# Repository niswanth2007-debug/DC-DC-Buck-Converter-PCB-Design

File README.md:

# LM2596T-5 DC to DC Buck Converter

A fixed 5V output buck converter PCB designed using KiCad as a first PCB design project.
This board steps down a higher DC voltage (7V–40V) to a stable 5V output using the
LM2596T-5 switching regulator IC.

---

## Overview

Buck converters are switching regulators that efficiently step down voltage with
minimal heat compared to linear regulators like the 7805. This design uses the
LM2596T-5, a fixed 5V variant that requires minimal external components while
delivering up to 3A of output current.

The board includes:
- An ON/OFF push button switch for manual control
- An LED power indicator with current limiting resistor
- Input and output screw terminals for easy wiring
- Flyback diode (1N5822) for protection
- Input and output filter capacitors for stable operation

---

## PCB Images

### Schematic

### 3D Tilted View

### 3D Top View

### Footprint Assignments

### PCB Editor View

---

## Schematic Overview

The circuit follows the standard LM2596 application circuit:
- **VIN** receives input from J2 screw terminal through C1 (680µF filter cap)
- **SW1** (push button) controls the ON/OFF pin of the LM2596
- **OUT** drives current through L1 (33µH inductor) to the output
- **D1** (1N5822 Schottky diode) acts as a freewheeling diode
- **C2** (220µF) filters the output voltage
- **FB** pin is tied to fixed 5V reference internally
- Output feeds J1 screw terminal with R1+D2 as a power indicator LED

---

## Components / Bill of Materials

| Ref  | Value      | Description                        | Footprint                        |
|------|------------|------------------------------------|----------------------------------|
| U1   | LM2596T-5  | Fixed 5V Buck Regulator IC         | TO-220-5, P3.4x3.7mm            |
| L1   | 33µH       | Inductor                           | Axial, L5.3mm D2.2mm P7.62mm   |
| C1   | 680µF      | Input Filter Capacitor             | Axial, L5.1mm D3.1mm P10.00mm  |
| C2   | 220µF      | Output Filter Capacitor            | Axial, L5.1mm D3.1mm P10.00mm  |
| D1   | 1N5822     | Schottky Freewheeling Diode        | DO-41, SOD81 P7.62mm            |
| D2   | LED        | Power Indicator LED                | LED_D3.0mm                      |
| R1   | 15Ω        | LED Current Limiting Resistor      | Axial, DIN0204 L3.6mm P5.08mm  |
| SW1  | SW_Push    | ON/OFF Push Button Switch          | SW_PUSH_6mm                     |
| J1   | Screw Term | Output Terminal (2-pin)            | Phoenix MKDS-1,5 2-pin          |
| J2   | Screw Term | Input Terminal (2-pin)             | Phoenix MKDS-1,5 2-pin          |

---

## Specifications

| Parameter           | Value          |
|--------------------|----------------|
| Input Voltage      | 7V – 40V DC    |
| Output Voltage     | 5V DC (Fixed)  |
| Max Output Current | Up to 3A       |
| Switching Frequency| 150kHz         |
| Efficiency         | Up to ~85%     |
| Inductor           | 33µH           |

---

## How to Use

### Input
Connect a DC power source (7V–40V) to the **J2** screw terminal:
- J2 Pin 1 → Positive (+)
- J2 Pin 2 → Negative (GND)

### Output
Connect your load to the **J1** screw terminal:
- J1 Pin 1 → 5V Output (+)
- J1 Pin 2 → Negative (GND)

### Power Switch
Press **SW1** to toggle the converter ON or OFF.
The **D2 LED** will light up when the output is active.

---

## How to Open in KiCad

1. Install [KiCad](https://www.kicad.org/) (version 9 or later recommended)
2. Clone or download this repository
3. Open `project 3.kicad_pro` in KiCad
4. Schematic is in `project 3.kicad_sch`
5. PCB layout is in `project 3.kicad_pcb`

---

## Generating Gerber Files

Gerber files are not included but can be easily generated:

1. Open `project 3.kicad_pcb` in KiCad PCB Editor
2. Go to **File → Plot**
3. Select layers: F.Cu, B.Cu, F.Silkscreen, B.Silkscreen,
   F.Mask, B.Mask, Edge.Cuts
4. Click **Plot**
5. Click **Generate Drill Files**
6. Submit output folder to your PCB manufacturer (JLCPCB, PCBWay, etc.)

---

## What I Learned

- KiCad schematic capture and PCB layout workflow
- Footprint assignment and 3D visualization
- Buck converter operating principles
- Through-hole component placement and routing
- Design rule checks (DRC) in KiCad

---

## Author

**Niswanth B**
Student ID: 128004168

*First KiCad PCB Design Project*

---

## License

This project is open source under the [MIT License](LICENSE).
Feel free to use, modify, and learn from it.

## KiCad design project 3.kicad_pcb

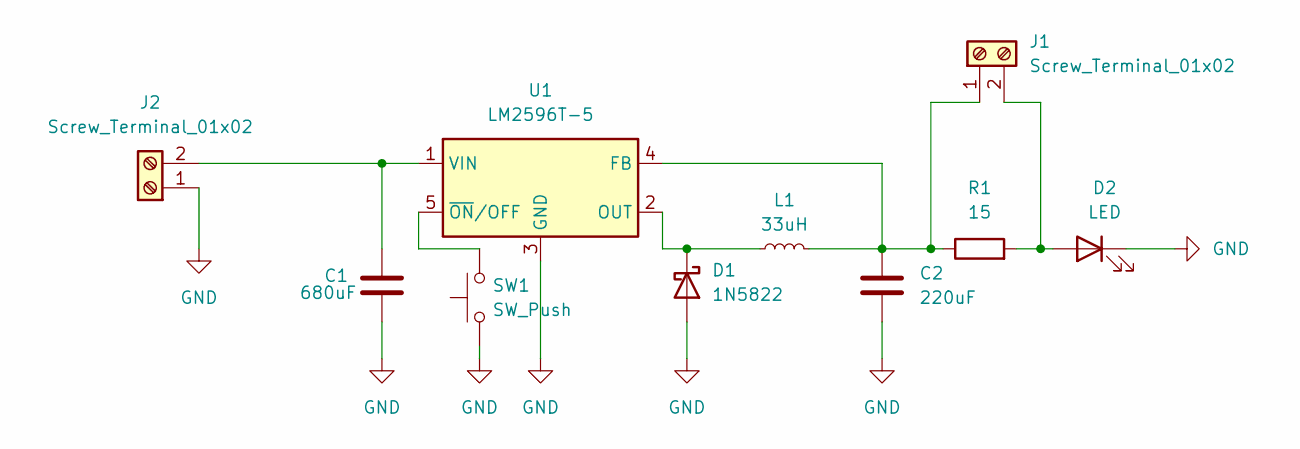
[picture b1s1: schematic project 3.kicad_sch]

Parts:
C1: 680uF; C_Axial_L5.1mm_D3.1mm_P10.00mm_Horizontal
C2: 220uF; C_Axial_L5.1mm_D3.1mm_P10.00mm_Horizontal
D1: 1N5822; D_DO-41_SOD81_P7.62mm_Horizontal
D2: LED; LED_D3.0mm
J1, J2: Screw_Terminal_01x02; TerminalBlock_Phoenix_MKDS-1,5-2_1x02_P5.00mm_Horizontal
L1: 33uH; L_Axial_L5.3mm_D2.2mm_P7.62mm_Horizontal_Vishay_IM-1
R1: 15; R_Axial_DIN0204_L3.6mm_D1.6mm_P5.08mm_Horizontal
SW1: SW_Push; SW_PUSH_6mm
U1: LM2596T-5; TO-220-5_P3.4x3.7mm_StaggerOdd_Lead3.8mm_Vertical

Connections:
GND: C1.2, C2.2, D1.2 (A), D2.1 (K), J2.1, SW1.1, U1.3 (GND)
unnamed: D1.1 (K), L1.1, U1.2 (OUT)
unnamed: D2.2 (A), J1.2, R1.2
unnamed: C2.1, J1.1, L1.2, R1.1, U1.4 (FB)
unnamed: C1.1, J2.2, U1.1 (VIN)
unnamed: SW1.2, U1.5 (~ON/OFF)

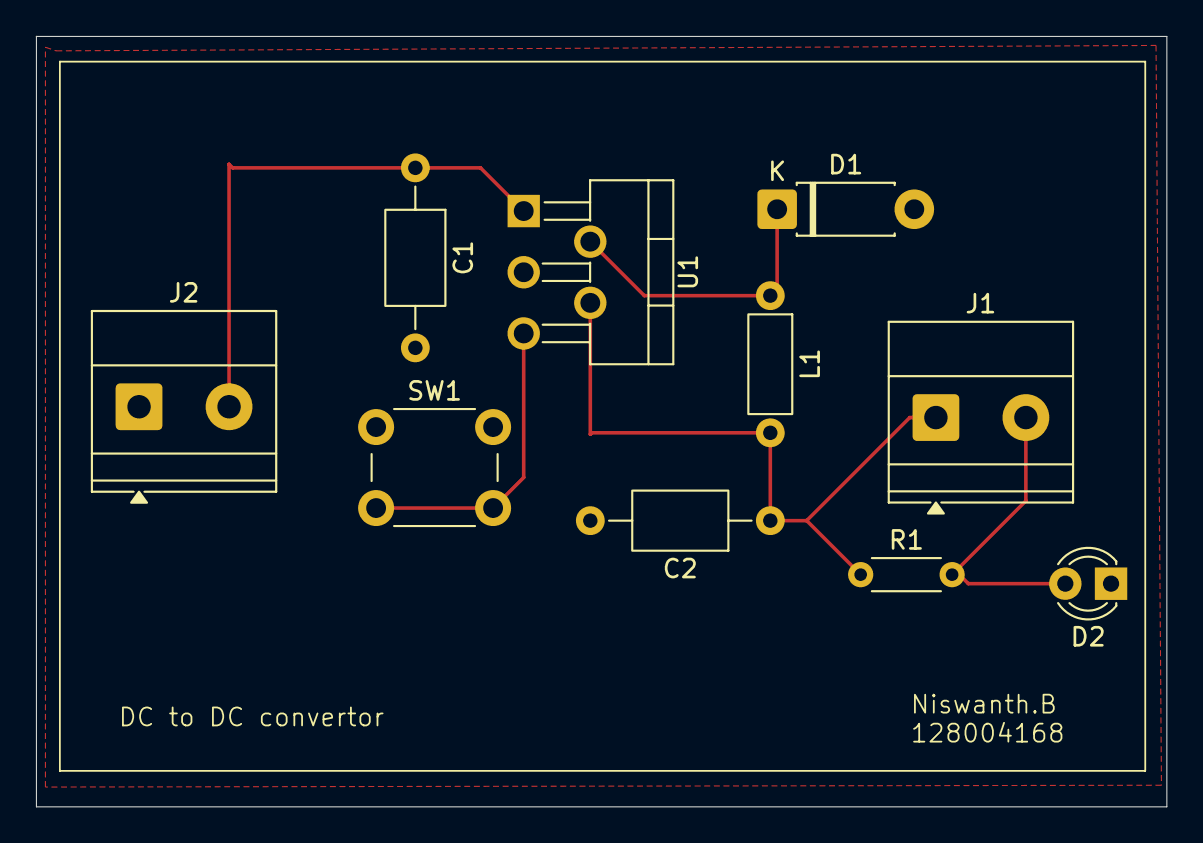
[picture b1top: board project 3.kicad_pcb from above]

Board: 2 copper layers, 62.8 x 42.8 mm, 10 parts (0 on the bottom side), 6 nets.

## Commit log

2026-06-05 Update README.md
    Added full project description including schematic overview,
    BOM table, specifications, usage instructions, and how to
    generate gerber files.
2026-06-05 Add files via upload
    Add KiCad project files (schematic, PCB, BOM)
2026-06-05 Add files via upload
    images
2026-06-05 Create images
2026-06-05 Rename pcb_editer_view.png to images/pcb_editer_view.png
2026-06-05 Rename top_view.png to images/top_view.png
2026-06-05 Rename schematic.png to images/schematic.png
2026-06-05 Rename tilted_view.png to images/tilted_view.png
2026-06-05 Rename footprints.png to images/footprints.png
